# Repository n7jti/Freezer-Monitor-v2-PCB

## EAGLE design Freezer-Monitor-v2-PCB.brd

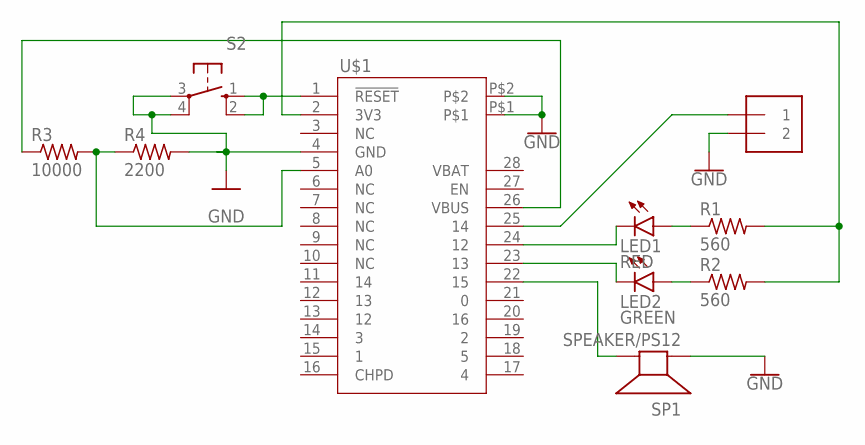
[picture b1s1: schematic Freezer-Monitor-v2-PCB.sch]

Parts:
J1: 1X2-3.5MM
LED1: RED; LED10MM
LED2: GREEN; LED10MM
R1, R2: 560; 0207/9
R3: 10000; 0207/9
R4: 2200; 0207/9
S2: 10-XX; B3F-10XX
SP1: SPEAKER/PS12; PS12
U$1: FEATHER_ESP8266_HUZZAHFEATHER_HUZZAH; FEATHER

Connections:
GND: J1.2, R4.2, S2.3, S2.4 (P1), SP1.P$1 (+), U$1.4 (GND), U$1.P$1, U$1.P$2
unnamed: R1.2, R2.2, U$1.2 (3V3)
unnamed: LED1.A, R1.1
unnamed: LED2.A, R2.1
unnamed: LED1.K (C), U$1.24 (12)
unnamed: LED2.K (C), U$1.23 (13)
unnamed: J1.1, U$1.25 (14)
unnamed: SP1.P$2 (-), U$1.22 (15)
unnamed: R3.2, R4.1, U$1.5 (A0)
unnamed: R3.1, U$1.26 (VBUS)
unnamed: S2.1 (S), S2.2 (S1), U$1.1 (!RESET)
VBAT: U$1.28 (VBAT)

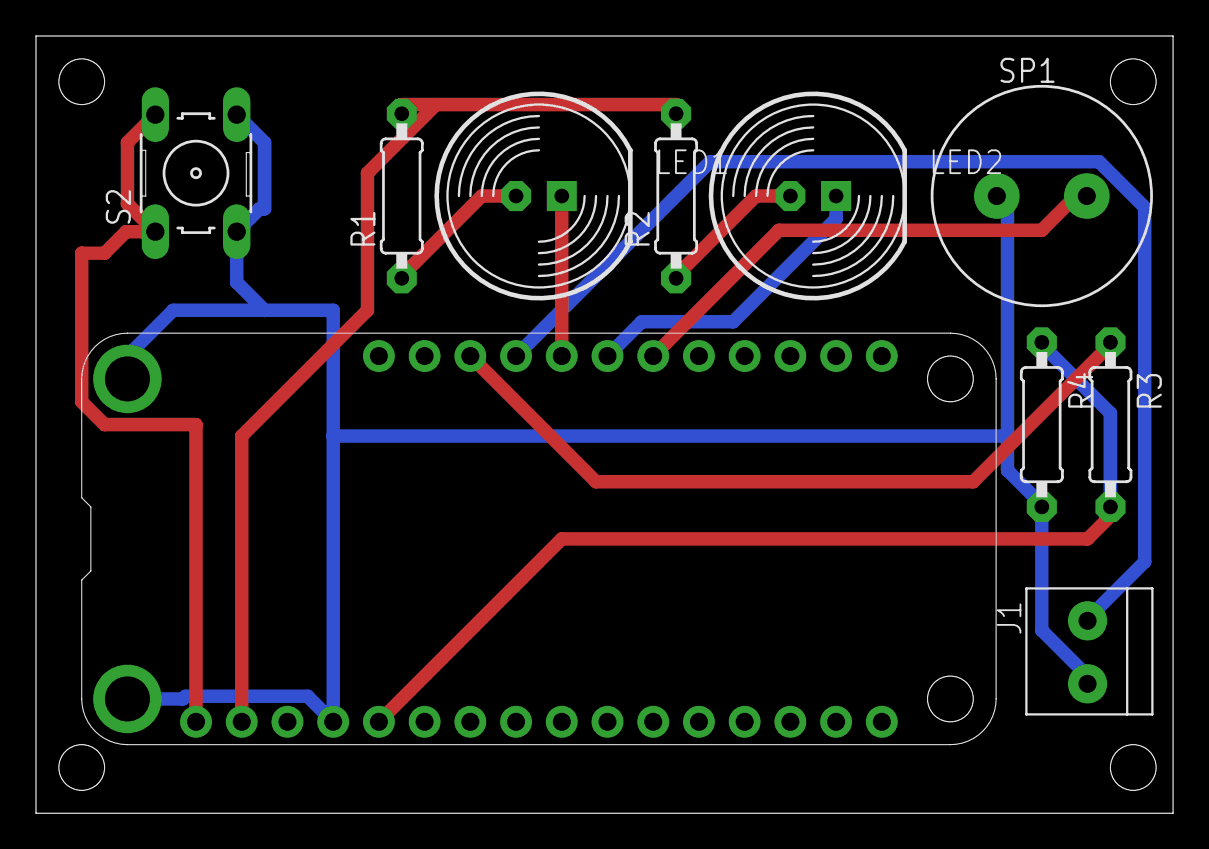
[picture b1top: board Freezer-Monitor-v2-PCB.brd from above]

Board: 2 copper layers, 63.2 x 43.2 mm, 10 parts (0 on the bottom side), 11 nets.

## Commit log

2019-06-07 Add the actual Eagle Files to the repo

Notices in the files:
parts and their libraries:
SparkFun-PowerSymbols: Licensing: Creative Commons ShareAlike 4.0 International - https://creativecommons.org/licenses/by-sa/4.0
